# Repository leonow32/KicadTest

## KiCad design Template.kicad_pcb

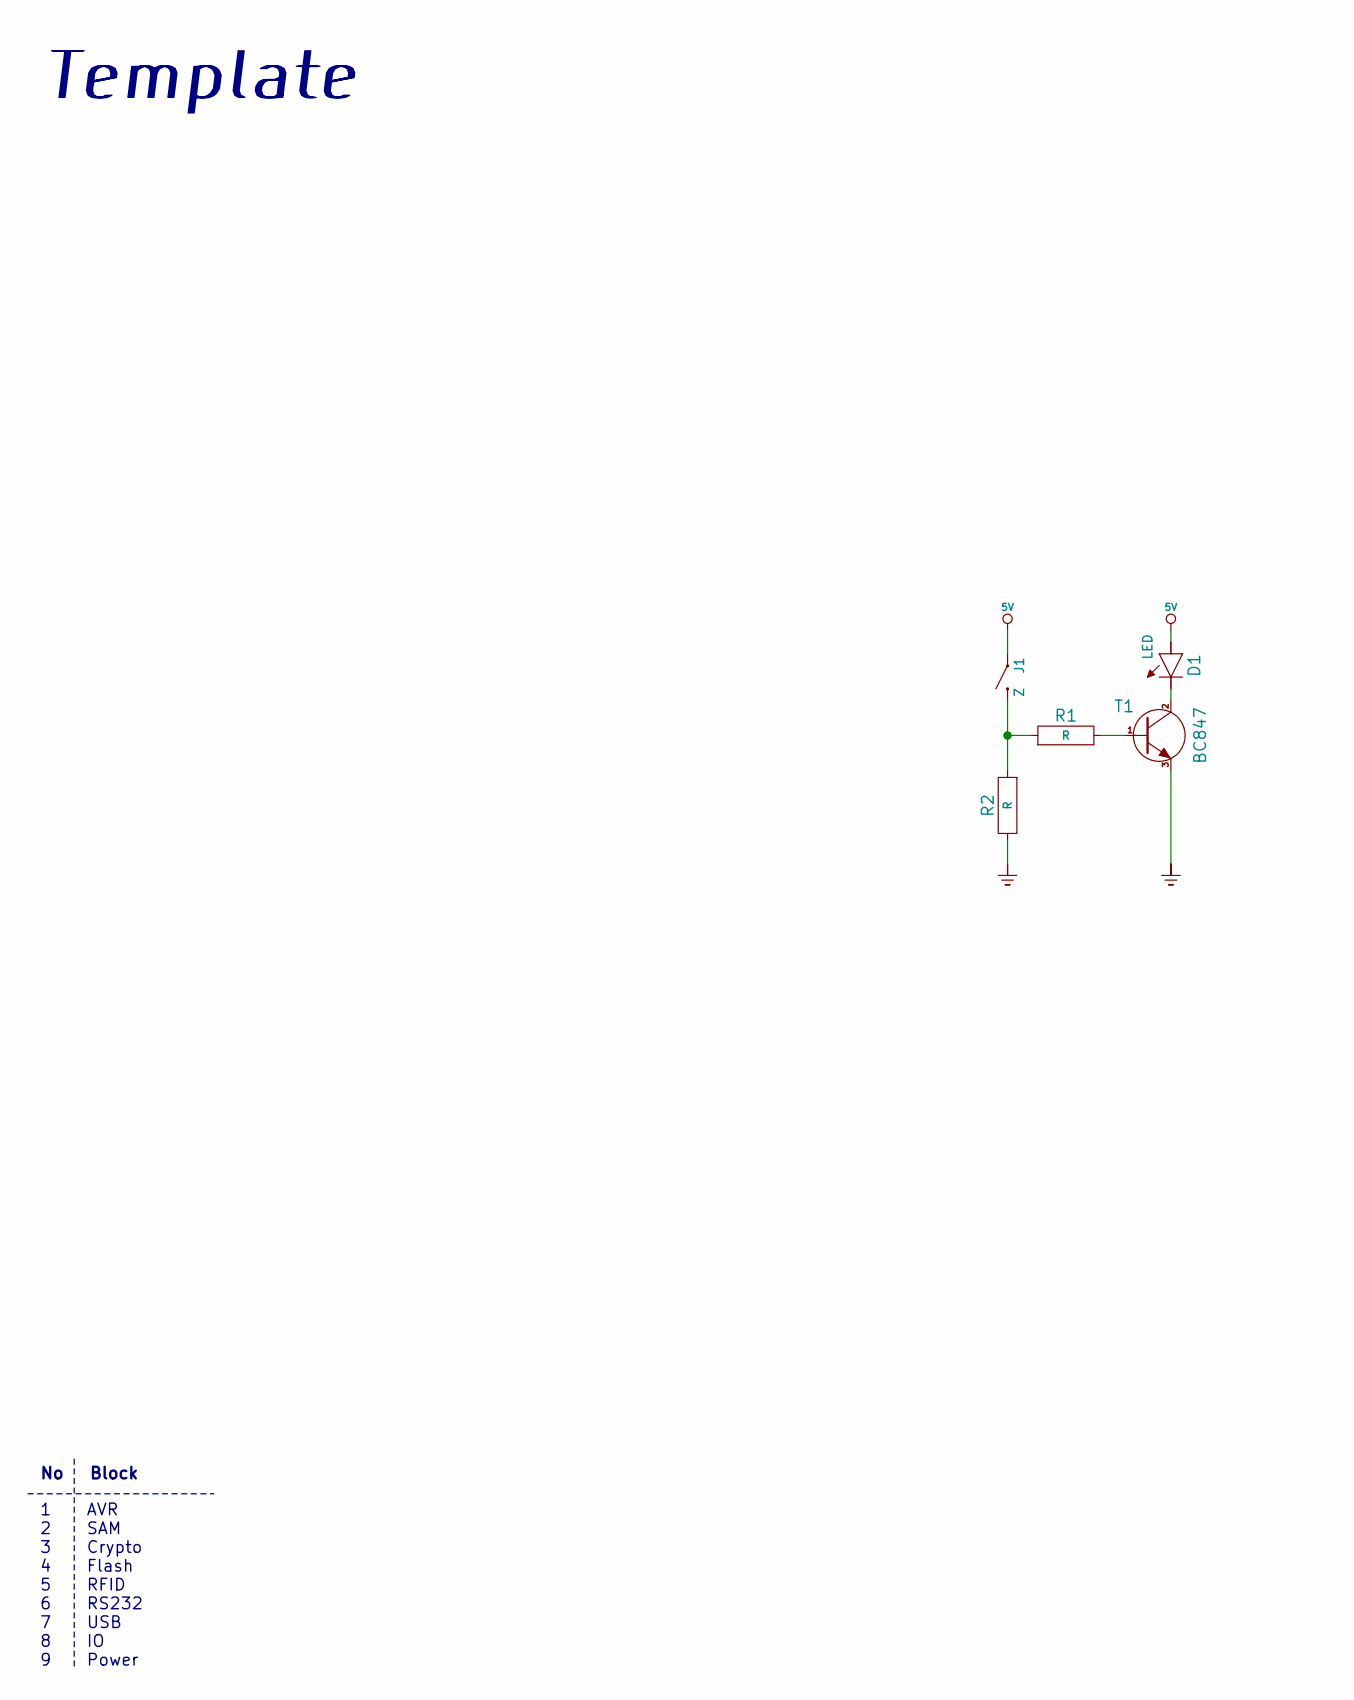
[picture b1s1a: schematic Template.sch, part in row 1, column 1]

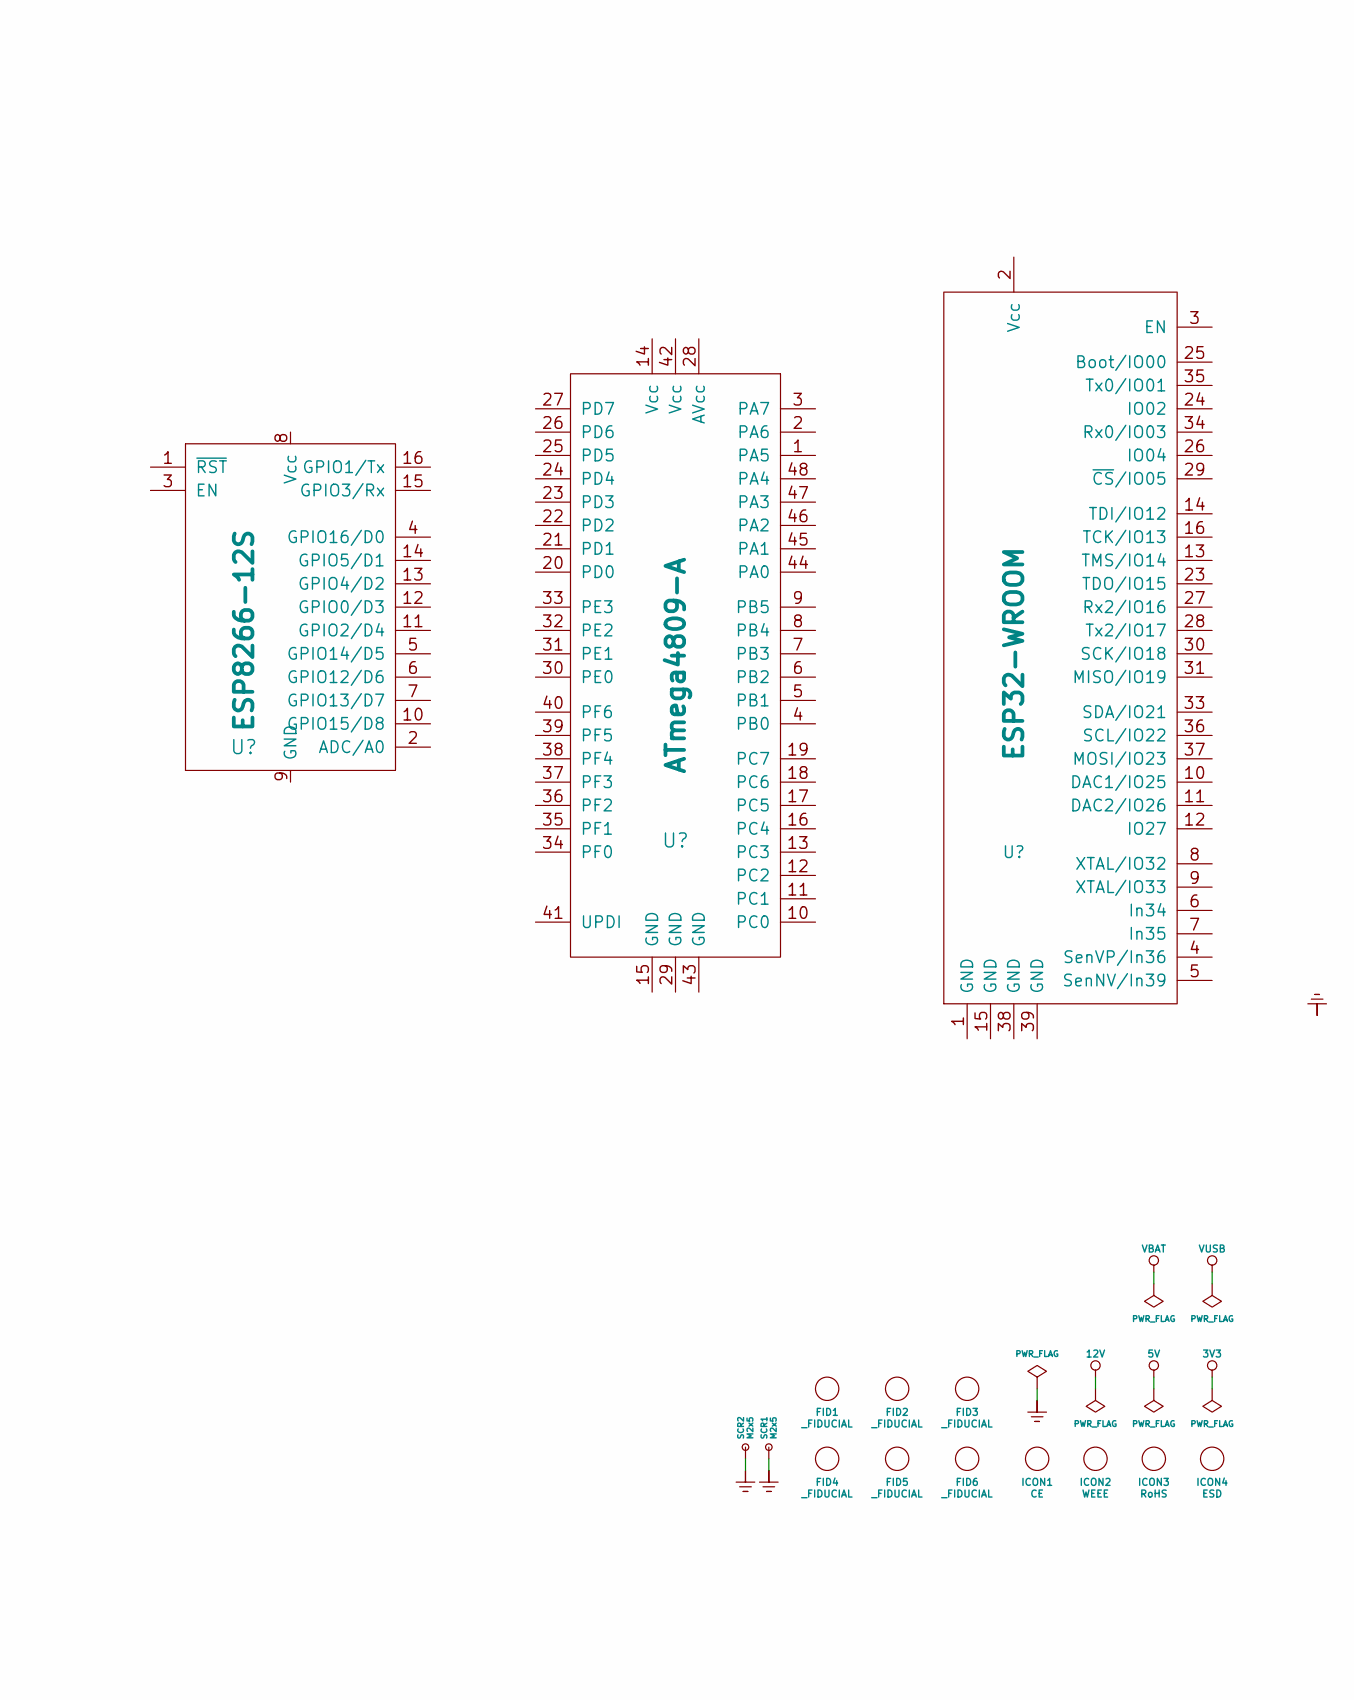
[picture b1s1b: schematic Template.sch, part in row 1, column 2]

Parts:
D1: LED; LED_1206
FID1, FID2, FID3, FID4, FID5, FID6: _FIDUCIAL; Fiducial_1.00mm_ring0.5mm
ICON1: CE; Logo_silk_CE_5x3.6mm
ICON2: WEEE; Logo_silk_WEEE_3.4x5mm
ICON3: RoHS; Logo_silk_ROHS_5x2.8mm
ICON4: ESD; ESD-Logo_6.6x6mm_SilkScreen
J1: Z; TACT_3x2.4_SMD
R1, R2: R; R_1206
SCR1, SCR2: M2x5; MountingHole_2.2mm_M2_Pad_Via
T1: BC847; SOT23

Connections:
5V: D1.2 (A), J1.2
GND: R2.2, SCR1.1, SCR2.1, T1.3
unnamed: D1.1 (K), T1.2
unnamed: J1.1, R1.1, R2.1
unnamed: R1.2, T1.1

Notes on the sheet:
No Block
1 AVR 2 SAM 3 Crypto 4 Flash 5 RFID 6 RS232 7 USB 8 IO 9 Power
Template

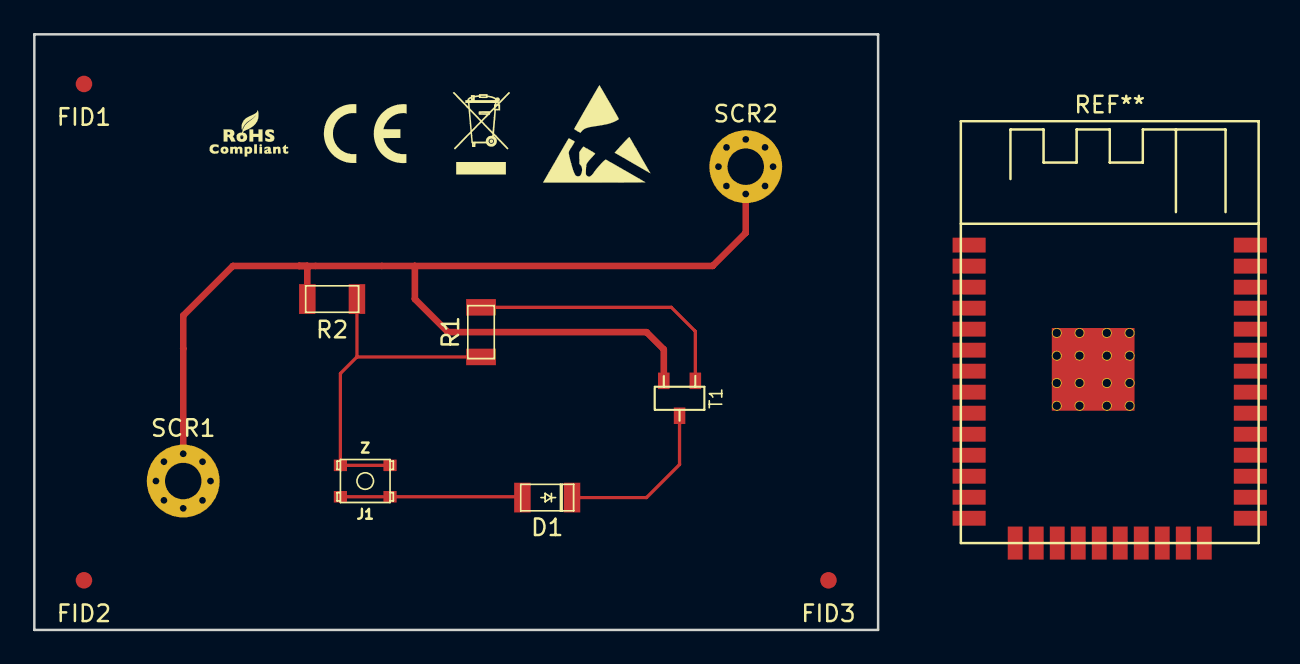
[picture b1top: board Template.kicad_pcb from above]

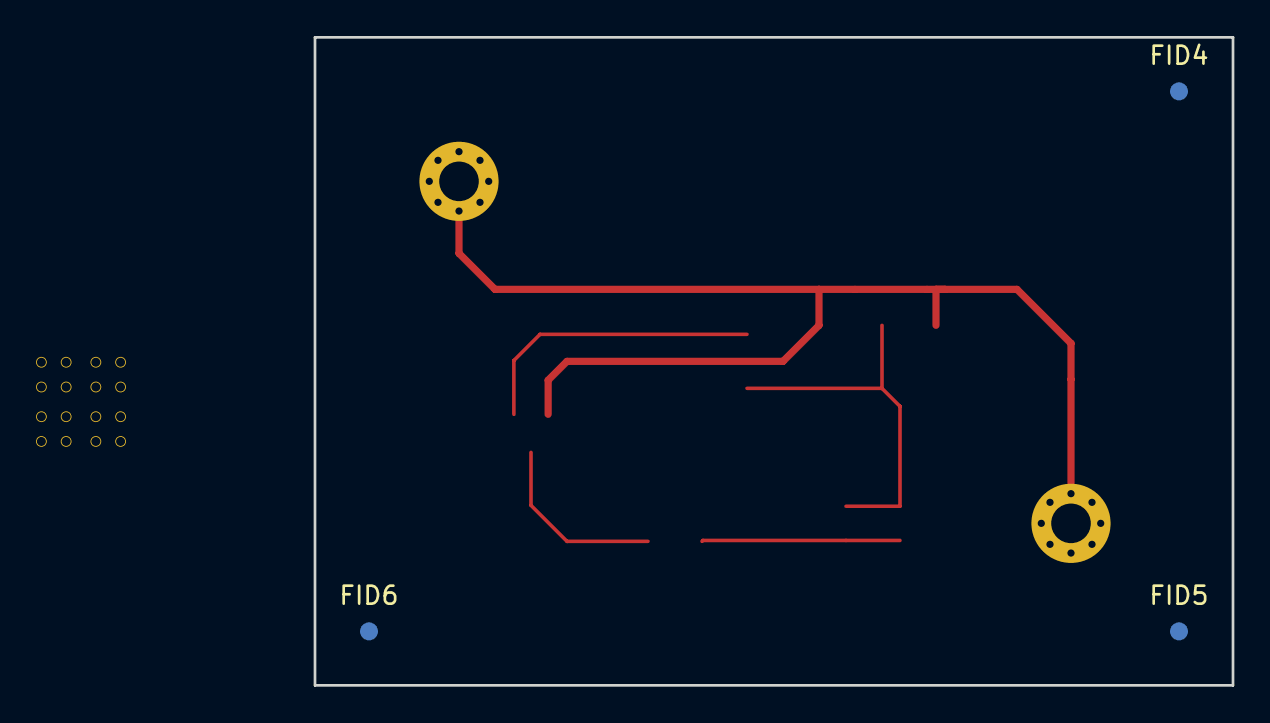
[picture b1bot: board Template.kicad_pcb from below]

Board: 2 copper layers, 51.0 x 36.0 mm, 17 parts (3 on the bottom side), 5 nets.

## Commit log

2020-10-23 Template
2020-10-23 Testowa modyfikacja
2020-10-23 Testowa zmiana schematu i plytki
2020-10-24 Added ESP32-WROOM
